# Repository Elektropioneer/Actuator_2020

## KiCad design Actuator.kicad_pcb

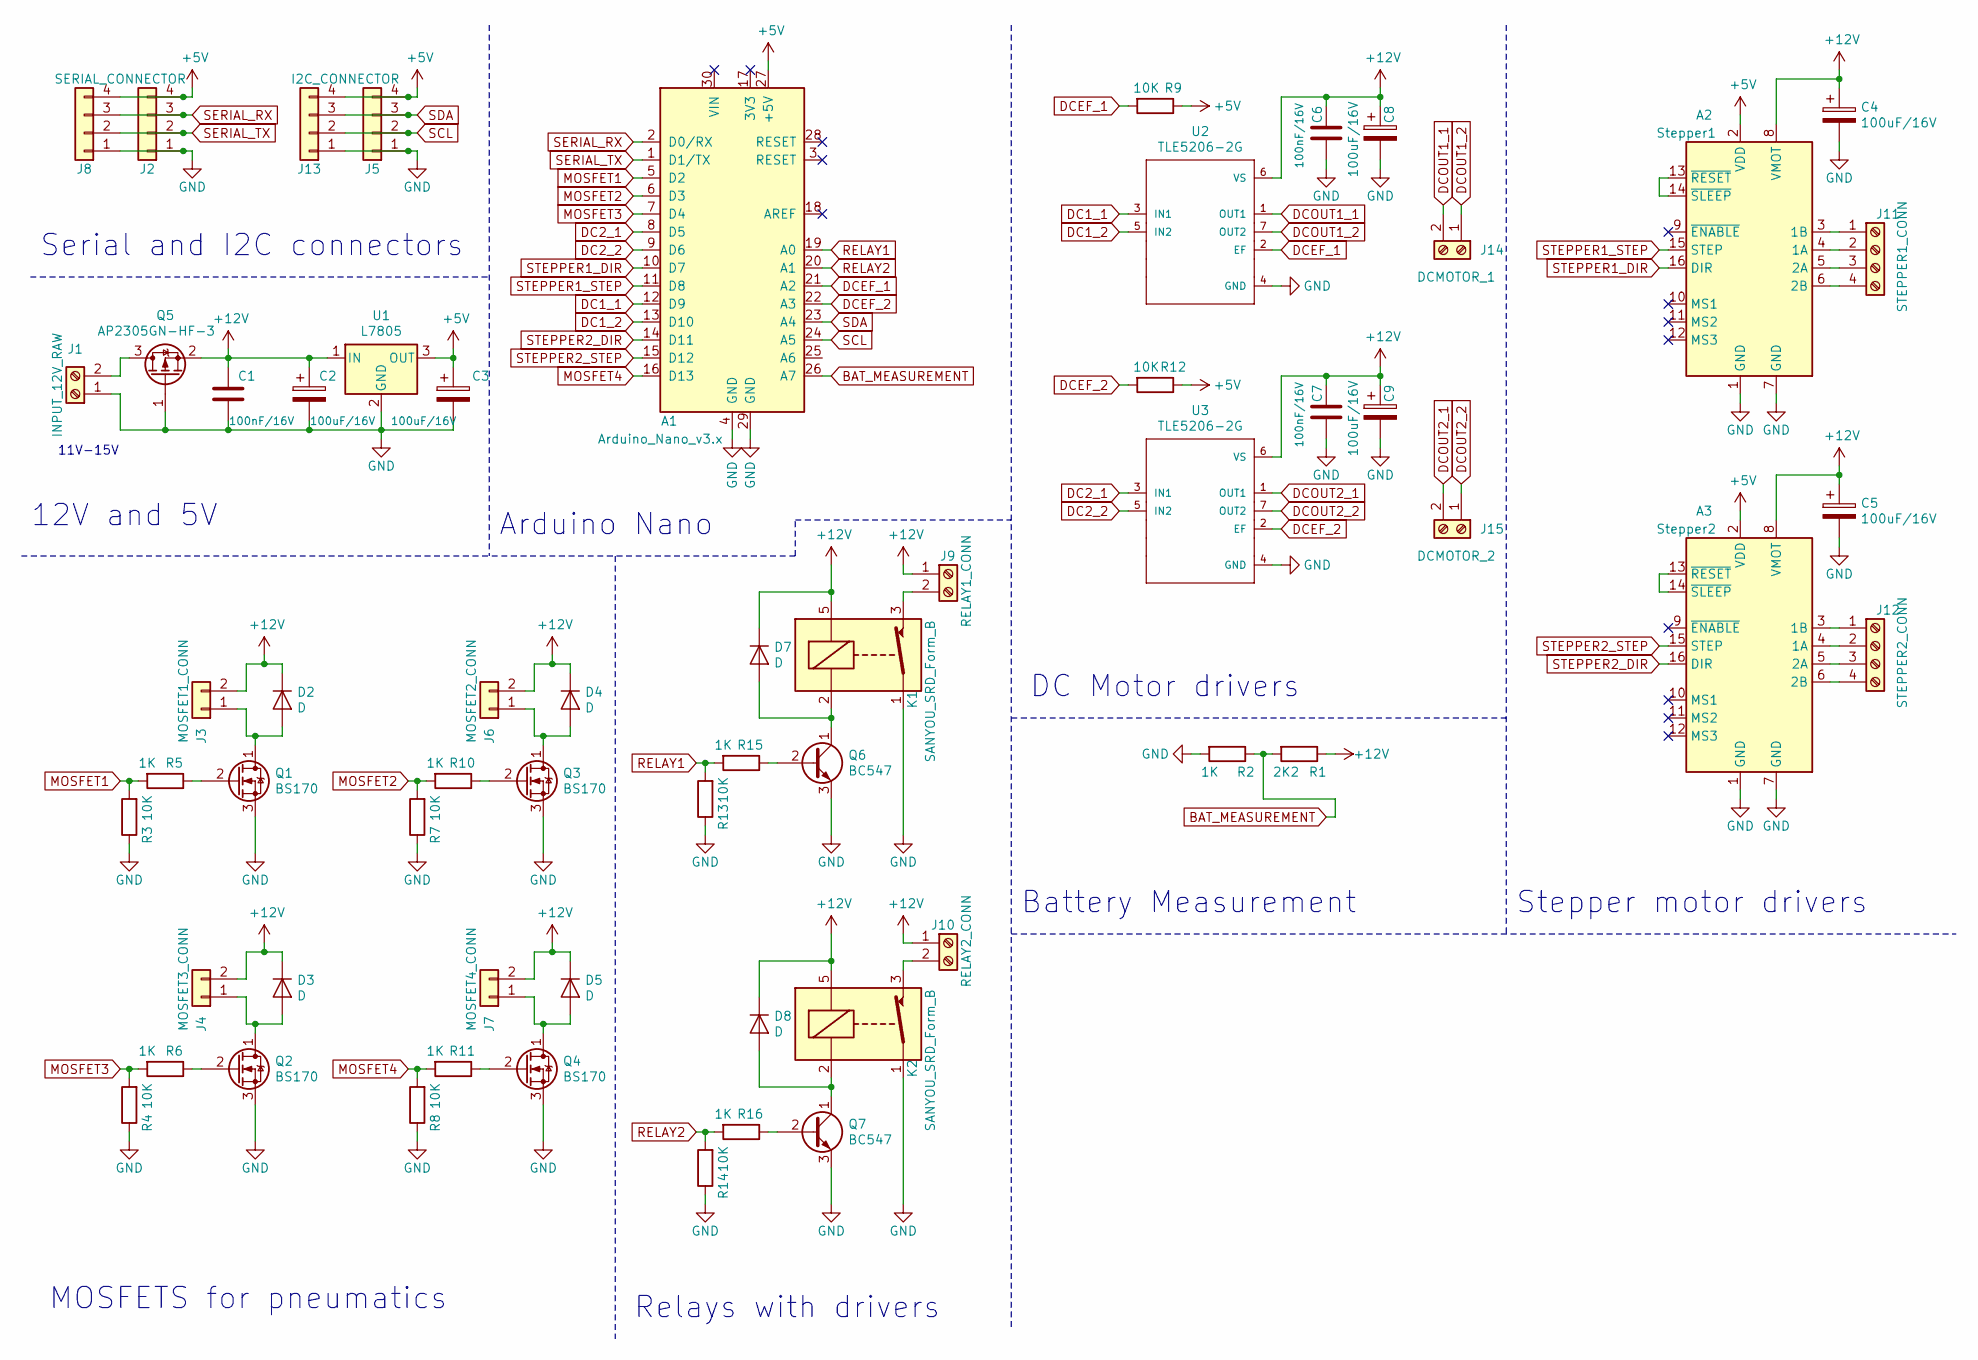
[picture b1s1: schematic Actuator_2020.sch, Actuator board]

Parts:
A1: Arduino_Nano_v3.x; Arduino_Nano
A2: Stepper1; Pololu_Breakout-16_15.2x20.3mm
A3: Stepper2; Pololu_Breakout-16_15.2x20.3mm
C1, C6, C7: 100nF/16V; C_0603_1608Metric
C2, C3, C4, C5, C8, C9: 100uF/16V; CP_Elec_6.3x5.4
D2, D3, D4, D5, D7, D8: D; D_SMA
J1: INPUT_12V_RAW; TerminalBlock_Phoenix_MKDS-1,5-2-5.08_1x02_P5.08mm_Horizont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
J2: SERIAL_CONNECTOR; PinHeader_1x04_P2.54mm_Vertical
J3: MOSFET1_CONN; PinHeader_1x02_P2.54mm_Vertical
J4: MOSFET3_CONN; PinHeader_1x02_P2.54mm_Vertical
J5: I2C_CONNECTOR; PinHeader_1x04_P2.54mm_Vertical
J6: MOSFET2_CONN; PinHeader_1x02_P2.54mm_Vertical
J7: MOSFET4_CONN; PinHeader_1x02_P2.54mm_Vertical
J8: SERIAL_CONNECTOR; JST_EH_B04B-EH-A_1x04_P2.50mm_Vertical
J9: RELAY1_CONN; TerminalBlock_Phoenix_MKDS-1,5-2-5.08_1x02_P5.08mm_Horizont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
J10: RELAY2_CONN; TerminalBlock_Phoenix_MKDS-1,5-2-5.08_1x02_P5.08mm_Horizont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
J11: STEPPER1_CONN; TerminalBlock_Phoenix_MKDS-1,5-4-5.08_1x04_P5.08mm_Horizont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
J12: STEPPER2_CONN; TerminalBlock_Phoenix_MKDS-1,5-4-5.08_1x04_P5.08mm_Horizont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
J13: I2C_CONNECTOR; JST_EH_B04B-EH-A_1x04_P2.50mm_Vertical
J14: DCMOTOR_1; TerminalBlock_Phoenix_MKDS-1,5-2_1x02_P5.00mm_Horizontal
J15: DCMOTOR_2; TerminalBlock_Phoenix_MKDS-1,5-2_1x02_P5.00mm_Horizontal
K1, K2: SANYOU_SRD_Form_B; Relay_SPDT_SANYOU_SRD_Series_Form_C
Q1, Q2, Q3, Q4: BS170; TO-92_Inline
Q5: AP2305GN-HF-3; SOT-23
Q6, Q7: BC547; TO-92_Inline
R1: 2K2; R_0603_1608Metric
R2, R5, R6, R10, R11, R15, R16: 1K; R_0603_1608Metric
R3, R4, R7, R8, R9, R12, R13, R14: 10K; R_0603_1608Metric
U1: L7805; TO-252-2
U2, U3: TLE5206-2G; DPAK127P1500X440-8N

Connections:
+5V: A1.27 (+5V), A2.2 (VDD), A3.2 (VDD), C3.1, J2.4, J5.4, J8.4, J13.4, R9.1, R12.1, U1.3 (OUT)
+12V: A2.8 (VMOT), A3.8 (VMOT), C1.1, C2.1, C4.1, C5.1, C6.1, C7.1, C8.1, C9.1, D2.1 (K), D3.1 (K), D4.1 (K), D5.1 (K), D7.1 (K), D8.1 (K), J3.2, J4.2, J6.2, J7.2, J9.1, J10.1, K1.5, K2.5, Q5.2 (S), R1.1, U1.1 (IN), U2.6 (VS), U3.6 (VS)
BAT_MEASUREMENT: A1.26 (A7), R1.2, R2.1
DC1_1: A1.12 (D9), U2.3 (IN1)
DC1_2: A1.13 (D10), U2.5 (IN2)
DC2_1: A1.8 (D5), U3.3 (IN1)
DC2_2: A1.9 (D6), U3.5 (IN2)
DCEF_1: A1.21 (A2), R9.2, U2.2 (EF)
DCEF_2: A1.22 (A3), R12.2, U3.2 (EF)
DCOUT1_1: J14.2, U2.1 (OUT1)
DCOUT1_2: J14.1, U2.7 (OUT2)
DCOUT2_1: J15.2, U3.1 (OUT1)
DCOUT2_2: J15.1, U3.7 (OUT2)
GND: A1.4 (GND), A1.29 (GND), A2.1 (GND), A2.7 (GND), A3.1 (GND), A3.7 (GND), C1.2, C2.2, C3.2, C4.2, C5.2, C6.2, C7.2, C8.2, C9.2, J1.1, J2.1, J5.1, J8.1, J13.1, K1.1, K2.1, Q1.3 (S), Q2.3 (S), Q3.3 (S), Q4.3 (S), Q5.1 (G), Q6.3 (E), Q7.3 (E), R2.2, R3.1, R4.1, R7.1, R8.1, R13.1, R14.1, U1.2 (GND), U2.4 (GND), U3.4 (GND)
MOSFET1: A1.5 (D2), R3.2, R5.2
MOSFET2: A1.6 (D3), R7.2, R10.2
MOSFET3: A1.7 (D4), R4.2, R6.2
MOSFET4: A1.16 (D13), R8.2, R11.2
unnamed: A2.3 (1B), J11.1
unnamed: A2.4 (1A), J11.2
unnamed: A2.5 (2A), J11.3
unnamed: A2.6 (2B), J11.4
unnamed: A2.13 (~RESET), A2.14 (~SLEEP)
unnamed: A3.3 (1B), J12.1
unnamed: A3.4 (1A), J12.2
unnamed: A3.5 (2A), J12.3
unnamed: A3.6 (2B), J12.4
unnamed: A3.13 (~RESET), A3.14 (~SLEEP)
unnamed: D2.2 (A), J3.1, Q1.1 (D)
unnamed: D3.2 (A), J4.1, Q2.1 (D)
unnamed: D4.2 (A), J6.1, Q3.1 (D)
unnamed: D5.2 (A), J7.1, Q4.1 (D)
unnamed: D7.2 (A), K1.2, Q6.1 (C)
unnamed: D8.2 (A), K2.2, Q7.1 (C)
unnamed: J1.2, Q5.3 (D)
unnamed: J9.2, K1.3
unnamed: J10.2, K2.3
unnamed: Q1.2 (G), R5.1
unnamed: Q2.2 (G), R6.1
unnamed: Q3.2 (G), R10.1
unnamed: Q4.2 (G), R11.1
unnamed: Q6.2 (B), R15.1
unnamed: Q7.2 (B), R16.1
RELAY1: A1.19 (A0), R13.2, R15.2
RELAY2: A1.20 (A1), R14.2, R16.2
SCL: A1.24 (A5), J5.2, J13.2
SDA: A1.23 (A4), J5.3, J13.3
SERIAL_RX: A1.2 (D0/RX), J2.3, J8.3
SERIAL_TX: A1.1 (D1/TX), J2.2, J8.2
STEPPER1_DIR: A1.10 (D7), A2.16 (DIR)
STEPPER1_STEP: A1.11 (D8), A2.15 (STEP)
STEPPER2_DIR: A1.14 (D11), A3.16 (DIR)
STEPPER2_STEP: A1.15 (D12), A3.15 (STEP)

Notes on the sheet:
11V-15V
Serial and I2C connectors
12V and 5V
Arduino Nano
DC Motor drivers
Battery Measurement
Stepper motor drivers
Relays with drivers
MOSFETS for pneumatics

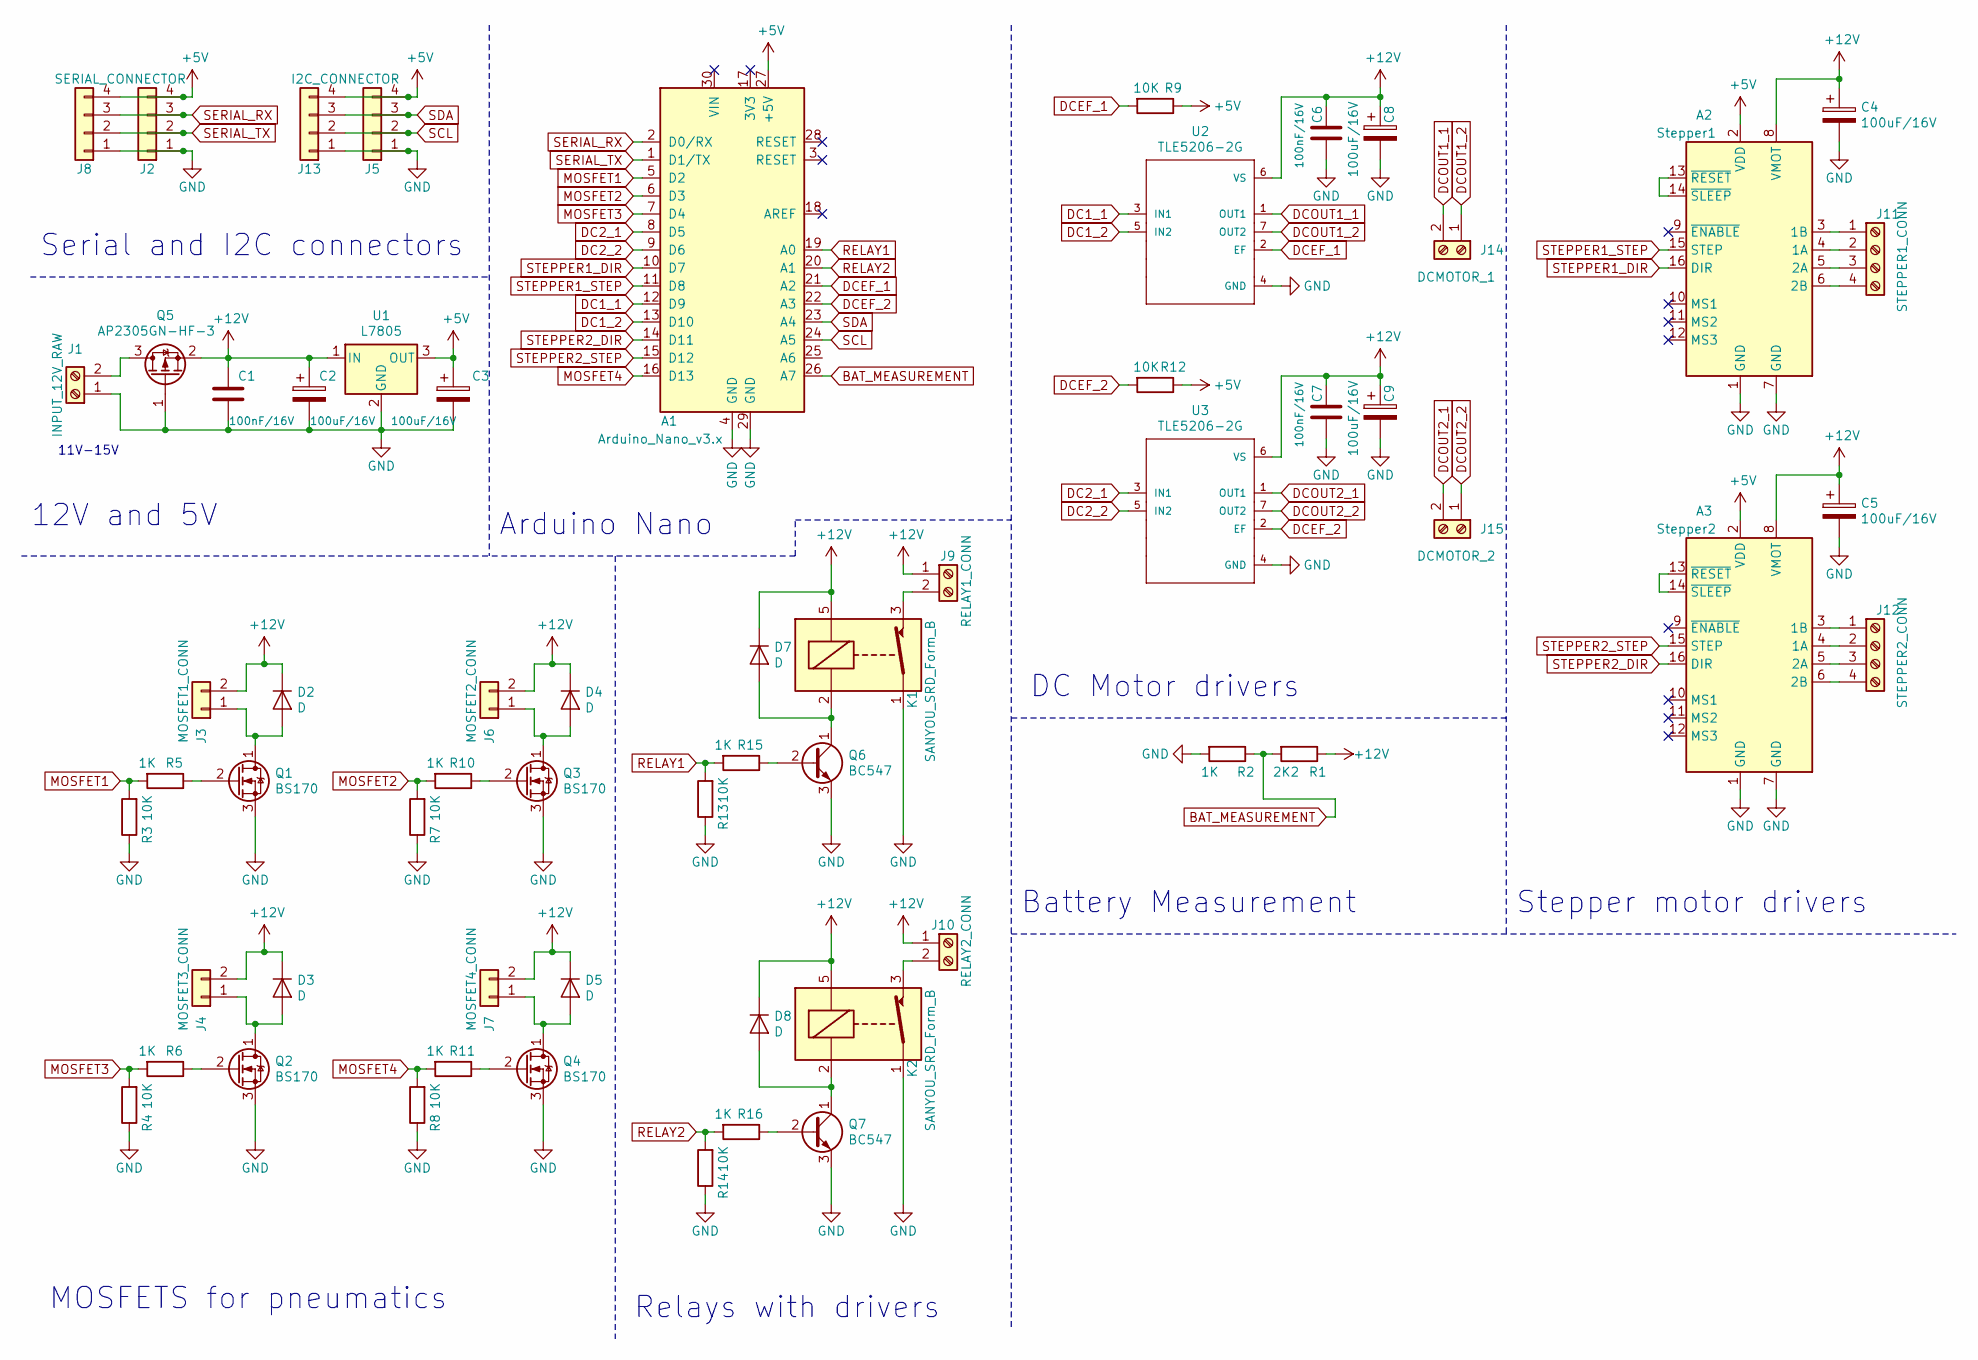
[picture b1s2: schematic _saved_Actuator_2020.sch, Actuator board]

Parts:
A1: Arduino_Nano_v3.x; Arduino_Nano
A2: Stepper1; Pololu_Breakout-16_15.2x20.3mm
A3: Stepper2; Pololu_Breakout-16_15.2x20.3mm
C1, C6, C7: 100nF/16V; C_0603_1608Metric
C2, C3, C4, C5, C8, C9: 100uF/16V; CP_Elec_6.3x5.4
D2, D3, D4, D5, D7, D8: D; D_SMA
J1: INPUT_12V_RAW; TerminalBlock_Phoenix_MKDS-1,5-2-5.08_1x02_P5.08mm_Horizont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
J2: SERIAL_CONNECTOR; PinHeader_1x04_P2.54mm_Vertical
J3: MOSFET1_CONN; PinHeader_1x02_P2.54mm_Vertical
J4: MOSFET3_CONN; PinHeader_1x02_P2.54mm_Vertical
J5: I2C_CONNECTOR; PinHeader_1x04_P2.54mm_Vertical
J6: MOSFET2_CONN; PinHeader_1x02_P2.54mm_Vertical
J7: MOSFET4_CONN; PinHeader_1x02_P2.54mm_Vertical
J8: SERIAL_CONNECTOR; JST_EH_B04B-EH-A_1x04_P2.50mm_Vertical
J9: RELAY1_CONN; TerminalBlock_Phoenix_MKDS-1,5-2-5.08_1x02_P5.08mm_Horizont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
J10: RELAY2_CONN; TerminalBlock_Phoenix_MKDS-1,5-2-5.08_1x02_P5.08mm_Horizont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
J11: STEPPER1_CONN; TerminalBlock_Phoenix_MKDS-1,5-4-5.08_1x04_P5.08mm_Horizont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
J12: STEPPER2_CONN; TerminalBlock_Phoenix_MKDS-1,5-4-5.08_1x04_P5.08mm_Horizont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
J13: I2C_CONNECTOR; JST_EH_B04B-EH-A_1x04_P2.50mm_Vertical
J14: DCMOTOR_1; TerminalBlock_Phoenix_MKDS-1,5-2_1x02_P5.00mm_Horizontal
J15: DCMOTOR_2; TerminalBlock_Phoenix_MKDS-1,5-2_1x02_P5.00mm_Horizontal
K1, K2: SANYOU_SRD_Form_B; Relay_SPDT_SANYOU_SRD_Series_Form_C
Q1, Q2, Q3, Q4: BS170; TO-92_Inline
Q5: AP2305GN-HF-3; SOT-23
Q6, Q7: BC547; TO-92_Inline
R1: 2K2; R_0603_1608Metric
R2, R5, R6, R10, R11, R15, R16: 1K; R_0603_1608Metric
R3, R4, R7, R8, R9, R12, R13, R14: 10K; R_0603_1608Metric
U1: L7805; TO-252-2
U2, U3: TLE5206-2G; DPAK127P1500X440-8N

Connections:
+5V: A1.27 (+5V), A2.2 (VDD), A3.2 (VDD), C3.1, J2.4, J5.4, J8.4, J13.4, R9.1, R12.1, U1.3 (OUT)
+12V: A2.8 (VMOT), A3.8 (VMOT), C1.1, C2.1, C4.1, C5.1, C6.1, C7.1, C8.1, C9.1, D2.1 (K), D3.1 (K), D4.1 (K), D5.1 (K), D7.1 (K), D8.1 (K), J3.2, J4.2, J6.2, J7.2, J9.1, J10.1, K1.5, K2.5, Q5.2 (S), R1.1, U1.1 (IN), U2.6 (VS), U3.6 (VS)
BAT_MEASUREMENT: A1.26 (A7), R1.2, R2.1
DC1_1: A1.12 (D9), U2.3 (IN1)
DC1_2: A1.13 (D10), U2.5 (IN2)
DC2_1: A1.8 (D5), U3.3 (IN1)
DC2_2: A1.9 (D6), U3.5 (IN2)
DCEF_1: A1.21 (A2), R9.2, U2.2 (EF)
DCEF_2: A1.22 (A3), R12.2, U3.2 (EF)
DCOUT1_1: J14.2, U2.1 (OUT1)
DCOUT1_2: J14.1, U2.7 (OUT2)
DCOUT2_1: J15.2, U3.1 (OUT1)
DCOUT2_2: J15.1, U3.7 (OUT2)
GND: A1.4 (GND), A1.29 (GND), A2.1 (GND), A2.7 (GND), A3.1 (GND), A3.7 (GND), C1.2, C2.2, C3.2, C4.2, C5.2, C6.2, C7.2, C8.2, C9.2, J1.1, J2.1, J5.1, J8.1, J13.1, K1.1, K2.1, Q1.3 (S), Q2.3 (S), Q3.3 (S), Q4.3 (S), Q5.1 (G), Q6.3 (E), Q7.3 (E), R2.2, R3.1, R4.1, R7.1, R8.1, R13.1, R14.1, U1.2 (GND), U2.4 (GND), U3.4 (GND)
MOSFET1: A1.5 (D2), R3.2, R5.2
MOSFET2: A1.6 (D3), R7.2, R10.2
MOSFET3: A1.7 (D4), R4.2, R6.2
MOSFET4: A1.16 (D13), R8.2, R11.2
unnamed: A2.3 (1B), J11.1
unnamed: A2.4 (1A), J11.2
unnamed: A2.5 (2A), J11.3
unnamed: A2.6 (2B), J11.4
unnamed: A2.13 (~RESET), A2.14 (~SLEEP)
unnamed: A3.3 (1B), J12.1
unnamed: A3.4 (1A), J12.2
unnamed: A3.5 (2A), J12.3
unnamed: A3.6 (2B), J12.4
unnamed: A3.13 (~RESET), A3.14 (~SLEEP)
unnamed: D2.2 (A), J3.1, Q1.1 (D)
unnamed: D3.2 (A), J4.1, Q2.1 (D)
unnamed: D4.2 (A), J6.1, Q3.1 (D)
unnamed: D5.2 (A), J7.1, Q4.1 (D)
unnamed: D7.2 (A), K1.2, Q6.1 (C)
unnamed: D8.2 (A), K2.2, Q7.1 (C)
unnamed: J1.2, Q5.3 (D)
unnamed: J9.2, K1.3
unnamed: J10.2, K2.3
unnamed: Q1.2 (G), R5.1
unnamed: Q2.2 (G), R6.1
unnamed: Q3.2 (G), R10.1
unnamed: Q4.2 (G), R11.1
unnamed: Q6.2 (B), R15.1
unnamed: Q7.2 (B), R16.1
RELAY1: A1.19 (A0), R13.2, R15.2
RELAY2: A1.20 (A1), R14.2, R16.2
SCL: A1.24 (A5), J5.2, J13.2
SDA: A1.23 (A4), J5.3, J13.3
SERIAL_RX: A1.2 (D0/RX), J2.3, J8.3
SERIAL_TX: A1.1 (D1/TX), J2.2, J8.2
STEPPER1_DIR: A1.10 (D7), A2.16 (DIR)
STEPPER1_STEP: A1.11 (D8), A2.15 (STEP)
STEPPER2_DIR: A1.14 (D11), A3.16 (DIR)
STEPPER2_STEP: A1.15 (D12), A3.15 (STEP)

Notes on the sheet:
11V-15V
Serial and I2C connectors
12V and 5V
Arduino Nano
DC Motor drivers
Battery Measurement
Stepper motor drivers
Relays with drivers
MOSFETS for pneumatics

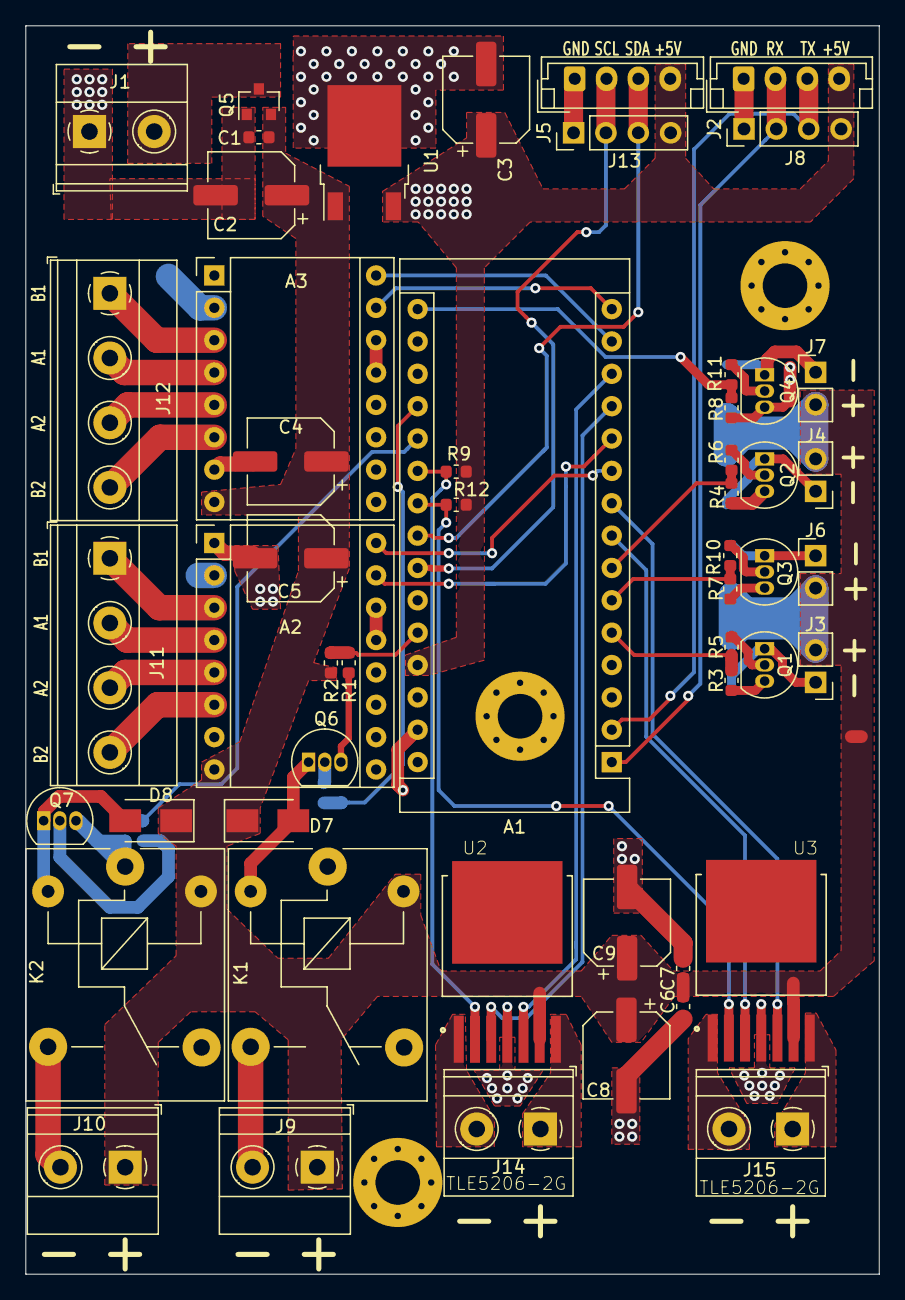
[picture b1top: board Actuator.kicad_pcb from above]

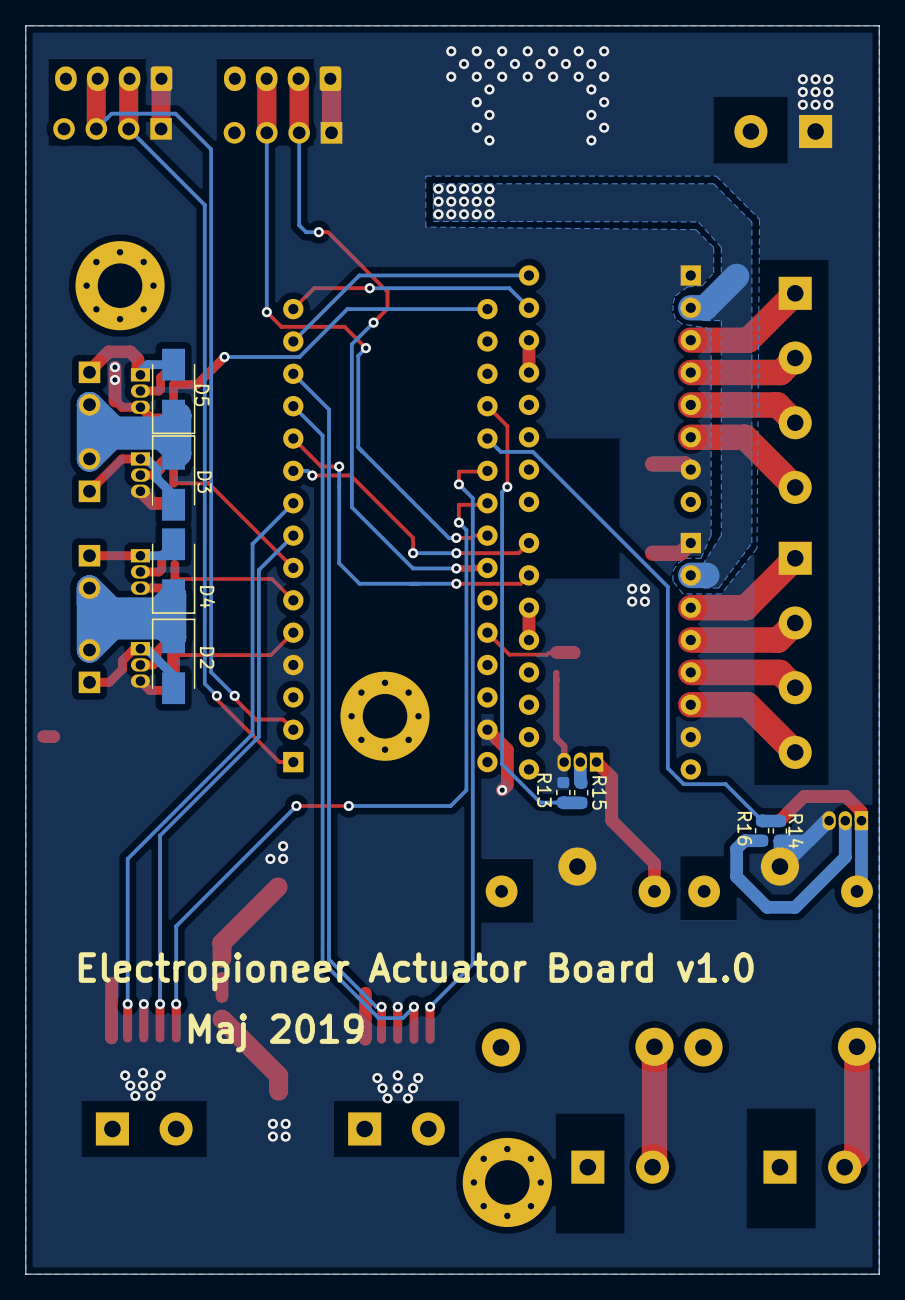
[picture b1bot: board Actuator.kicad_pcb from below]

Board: 2 copper layers, 67.0 x 98.0 mm, 61 parts (8 on the bottom side), 53 nets.

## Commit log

2019-05-08 dodatni fileovi
2019-05-09 Gerber_Act_2020
2019-05-09 Updated Gerbers
2019-05-09 Zipped Gerbers
